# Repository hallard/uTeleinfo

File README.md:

# Micro Téléinfo V3

Dongle USB permettant de récupérer les trames téléinformation

Suivez mes nouveautés et autres projets sur mon [blog][4] 

## Historique

**New V3.0**

- Remplacement R3 par un potentiomètre
- Led séparées RX / TX

**Prototype V3.0**

- Réduction taille PCB
- Ajout LED information signal TIC
- Test Led Rouge/Vert pour RX/TX
- Test avec connecteur USB PTH/SMD
- Ajustement résistance TIC 220 Ohm
- Ajustement résistance MOSFET 3.3KOhm
- Changement chip FT230XS par CH9106

**V2.0**

- Version historique

**V3.0 VS V2.0**

# Installation et configuration

Les tests suivants sont réalisés depuis un terminal (ou via SSH) sur Rapsberry PI, veillez à bien toujours avoir votre PI à jour avec les commandes suivantes

```shell
sudo apt-get update
sudo apt-get upgrade
```

## Verification du module

Lancer un terminal (ou via SSH), connecter le module puis faites un `dmesg -e`

```shell
[Dec27 11:25] usb 1-1.4: new full-speed USB device number 30 using dwc_otg
[  +0.144735] usb 1-1.4: New USB device found, idVendor=1a86, idProduct=55d4, bcdDevice= 4.43
[  +0.000022] usb 1-1.4: New USB device strings: Mfr=1, Product=2, SerialNumber=3
[  +0.000016] usb 1-1.4: Product: uTinfo-V3.0
[  +0.000015] usb 1-1.4: Manufacturer: CH2i
[  +0.000014] usb 1-1.4: SerialNumber: TINFO-2000
[  +0.001248] cdc_acm 1-1.4:1.0: ttyACM0: USB ACM device
```

On voit bien que le module est bien detecté, dans notre cas le nom de device `/dev/ttyACM0`

## Connecter la téléinfo

Brancher le connecteur vert du module avec un cable (un petit cable fait parfaitement l'affaire comme téléphonique, réseau, alim LED, ...) sur le compteur aux bornes I1 et I2, peut importe le sens ce n'est pas polarisé.

La Led bleu doit clignoter très rapidement (ou être quasi allumée) indiquant que le signal téléinfo est bien présent.

## Test de réception 

### Picocom

Le 1er test est avec un terminal série nommé `picocom` , installation via 

```shell
sudo apt-get install picocom
```

Puis lancer la commande suivante si vous êtes en mode historique
```shell
pi@pi03:~ # picocom -b 1200 -d 7 -p e -f n /dev/ttyACM0 
```

Ou celle ci en mode standard
```shell
pi@pi03:~ # picocom -b 9600 -d 7 -p e -f n /dev/ttyACM0 
```

Vous devriez voir arriver des données sur le termimal 

```shell
picocom v3.1

port is        : /dev/ttyACM0
flowcontrol    : none
baudrate is    : 1200
parity is      : even
databits are   : 7
stopbits are   : 1
escape is      : C-a
local echo is  : no
noinit is      : no
noreset is     : no
hangup is      : no
nolock is      : no
send_cmd is    : sz -vv
receive_cmd is : rz -vv -E
imap is        : 
omap is        : 
emap is        : crcrlf,delbs,
logfile is     : none
initstring     : none
exit_after is  : not set
exit is        : no

Type [C-a] [C-h] to see available commands
Terminal ready
HCHP 002784502 /
PTEC HP..  
IINST 001 X
IMAX 002 A
PAPP 00200 #
HHPHC A ,
MOTDETAT 000000 B
ADCO 021528603314 :
OPTARIF HC.. <
ISOUSC 15 <
HCHC 001096011 X
HCHP 002784502 /
PTEC HP..  
IINST 001 X
IMAX 002 A
PAPP 00180 *
HHPHC A ,
MOTDETAT 000000 B
ADCO 021528603314 :
OPTARIF HC.. <

Terminating...
Skipping tty reset...
Thanks for using picocom
root@pi03:~ # 

```

PS : Pour quitter picocom il faut faire `CTRL-A` puis immédiatement `CRTL-Q`

De plus lorsque picocom est actif et les données reçues par le PI la LED rouge doit aussi se mettre à clignoter 

### Test avec Python

Un programme de test basic a aussi été réalisé en python, vous trouverez toute la documentation sur le repo suivant
https://github.com/hallard/teleinfo-test

### Python avancé

Un programme plus avancé été réalisé en python (merci à l'auteur original), vous trouverez toute la documentation sur le repo suivant
https://github.com/hallard/python-teleinfo

### Python publication MQTT

En utilisant le module avancé ci dessous il est extrèmement simple de faire un script python qui publie les données dans MQTT

Installation de la librairie paho-mqtt et des outils MQTT

```shell
pi@pi03:~ # sudo apt-get install mosquitto-clients
pi@pi03:~ # pip install paho-mqtt
```

Créer le script suivant dans le dossier python-teleinfo, par exemple `test.py`

```python
#!/usr/bin/env python
import json
import paho.mqtt.client as mqtt
from teleinfo import Parser
from teleinfo.hw_vendors import UTInfo3
ti = Parser(UTInfo3())
client = mqtt.Client("PI-Demo1")
client.connect("test.mosquitto.org")
while True:
    data = json.dumps(ti.get_frame())
    print(data)
    client.publish("teleinfo/demo", data)
```

Puis le lancer via
```shell
pi@pi03:~/python-teleinfo $ python test.py 
```
Enfin ouvrez un autre shell sue le PI (ou lancer la commande sur votre ordinateur ou utiliser un outil type MQTT Explorer) et vérifier les publication dans MQTT

Et voila le résultat

```shell

pi@pi03:~ # mosquitto_sub -h test.mosquitto.org -t "teleinfo/#"
{"IINST": "001", "MOTDETAT": "000000", "OPTARIF": "HC..", "ADCO": "021528603314", "HCHC": "001096011", "PAPP": "00170", "IMAX": "002", "PTEC": "HP..", "ISOUSC": "15", "HHPHC": "A", "HCHP": "002785290"}
{"IINST": "001", "MOTDETAT": "000000", "OPTARIF": "HC..", "ADCO": "021528603314", "HCHC": "001096011", "PAPP": "00160", "IMAX": "002", "PTEC": "HP..", "ISOUSC": "15", "HHPHC": "A", "HCHP": "002785291"}
{"IINST": "001", "MOTDETAT": "000000", "OPTARIF": "HC..", "ADCO": "021528603314", "HCHC": "001096011", "PAPP": "00180", "IMAX": "002", "PTEC": "HP..", "ISOUSC": "15", "HHPHC": "A", "HCHP": "002785291"}
```

Bien entendu c'est un exemple, il faudrait parser les valeurs, potentiellement les convertir en nombre et faire un peu de gestion d'erreur mais les bases fonctionnelles sont là.

# Conception

**Schémas** 

**Cartes**  

# Support et discussions

Si vous rencontrez le moindre soucis ou si vous voulez simplement discuter de votre projet avec ce module n'hésitez pas à utiliser le [forum communautaire](https://community.ch2i.eu/category/9)

# License

This work is licensed under a [Creative Commons Attribution-NonCommercial-ShareAlike 4.0 International License](https://creativecommons.org/licenses/by-nc-sa/4.0/)    
If you want to do commercial stuff with this project, please contact [CH2i company](https://ch2i.eu/en#support) so we can organize an simple agreement.

# Trop compliqué de le fabriquer ? 

Vous pouvez commander ce module assemblé et prêt à l'emploi sur [tindie][1] ou sur [Lectronz](https://lectronz.com/products/utinfo).

Les clients européens peuvent préférer commander sur Lectronz, qui propose des moyens de paiement supplémentaires et des prix en euros.

[1]: https://www.tindie.com/products/28873/
[4]: http://hallard.me
[5]: http://hallard.me/teleinfo/
[6]: https://www.tindie.com/products/Hallard/micro-teleinfo/

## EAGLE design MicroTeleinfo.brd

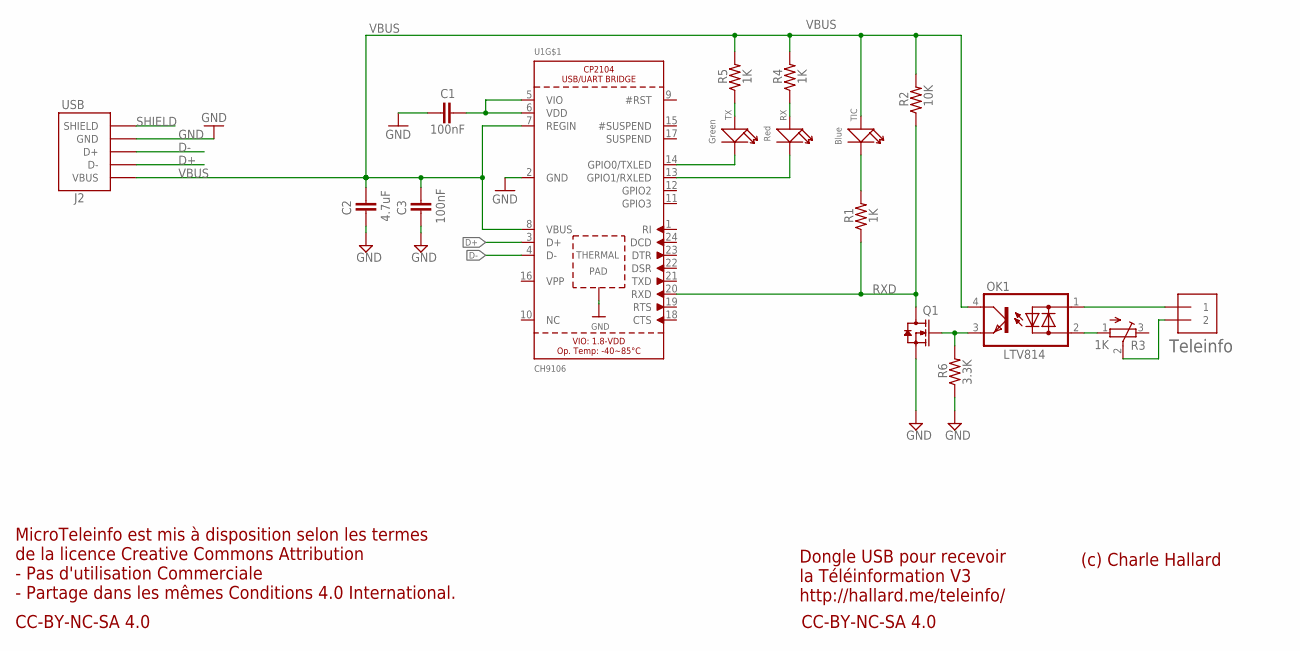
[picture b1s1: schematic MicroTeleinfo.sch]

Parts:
C1, C3: 100nF; 0402-CAP-OK
C2: 4.7uF; 0402-CAP-OK
J1: 1X2-3.5MM
J2: USB; GCT_USB1061-XX-X-X_REVA
OK1: LTV814; DIL4-SMD
Q1: CJ2302; SOT-323-3
R1, R4, R5: 1K; 0402-RES
R2: 10K; 0402-RES
R3: 1K; TC33X
R6: 3.3K; 0402-RES
RX: Red; LED-0402
TIC: Blue; LED-0402
TX: Green; LED-0402
U1: CH9106; QFN24_4MM_SMSC

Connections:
D+: J2.3 (D+), U1.3 (D+)
D-: J2.2 (D-), U1.4 (D-)
GND: C1.1, C2.2, C3.1, J2.4 (GND), Q1.2 (S), R6.1, U1.2 (GND), U1.THERM (TP)
unnamed: OK1.3 (E), Q1.1 (G), R6.2
unnamed: C1.2, U1.5 (VIO), U1.6 (VDD)
unnamed: OK1.2 (AC2), R3.1 (A)
unnamed: J1.1, OK1.1 (AC1)
unnamed: J1.2, R3.2 (S)
unnamed: R4.1, RX.+
unnamed: R5.1, TX.+
unnamed: R1.2, TIC.-
unnamed: TX.-, U1.14 (GPIO0/TXLED)
unnamed: RX.-, U1.13 (GPIO1/RXLED)
RXD: Q1.3 (D), R1.1, R2.1, U1.20 (RXD)
SHIELD: J2.5 (SHIELD), J2.6 (SHIELD)
VBUS: C2.1, C3.2, J2.1 (VBUS), OK1.4 (C), R2.2, R4.2, R5.2, TIC.+, U1.7 (REGIN), U1.8 (VBUS)

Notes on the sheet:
Dongle USB pour recevoir la Téléinformation V3 http://hallard.me/teleinfo/
Teleinfo
CC-BY-NC-SA 4.0
MicroTeleinfo est mis à disposition selon les termes de la licence Creative Commons Attribution - Pas d'utilisation Commerciale - Partage dans les mêmes Conditions 4.0 International.
(c) Charle Hallard

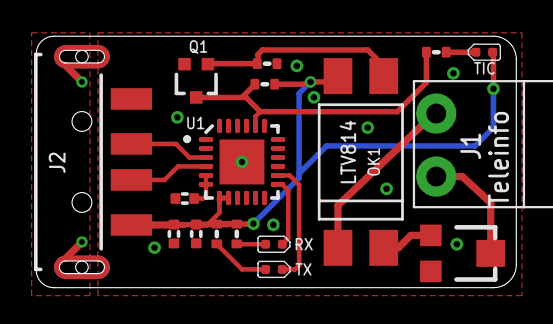
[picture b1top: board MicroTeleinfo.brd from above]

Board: 2 copper layers, 26.7 x 14.0 mm, 18 parts (1 on the bottom side), 16 nets.

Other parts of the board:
U$2: LOGO_CH2I_015_COPPER

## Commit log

2022-12-27 fix image links
2022-12-27 added mqtt script
2026-03-28 FACTORY : Updated procedure for new batch
    - Updated procedure for batch 2500-2749
    - Updated config file to start 2500-2749
    - added V1.2 version of flashing tool for reference
2026-04-26 docs: add Lectronz badges next to Tindie
2026-04-29 Switch to CC BY-NC-SA 4.0 license, add LICENSE file
2026-04-29 license: use pure CC BY-NC-SA 4.0 text for GitHub auto-detection
2026-04-29 license: add copyright header above CC BY-NC-SA 4.0 text

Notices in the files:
parts and their libraries:
microbuilder: This work is placed in the public domain, and may be freely used for commercial and non-commercial work with the following conditions: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
SparkFun: Licensing: CC v3.0 Share-Alike You are welcome to use this library for commercial purposes.
